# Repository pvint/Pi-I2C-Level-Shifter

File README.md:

# Pi-I2C-Level-Shifter
Level shifter to connect I2C bus on the Pi to +5v or other voltage devices (hardware)

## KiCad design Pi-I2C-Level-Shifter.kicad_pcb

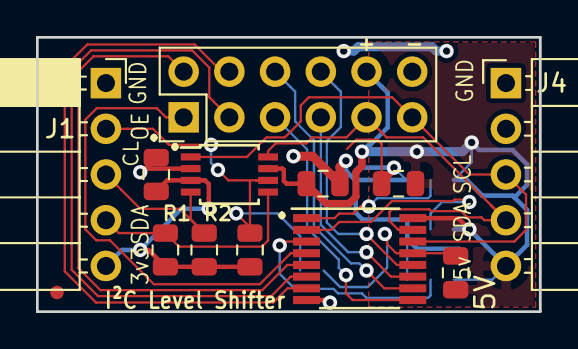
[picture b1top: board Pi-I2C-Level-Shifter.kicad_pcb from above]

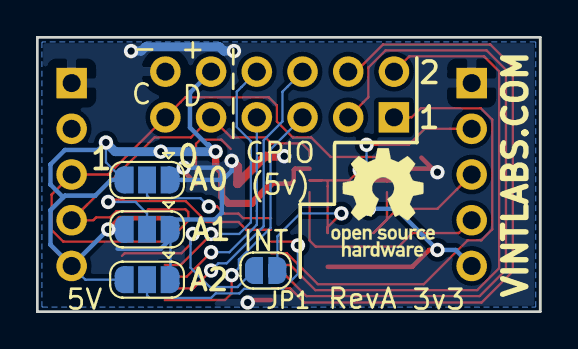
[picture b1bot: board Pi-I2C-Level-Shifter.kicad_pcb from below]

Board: 2 copper layers, 27.9 x 15.2 mm, 16 parts (4 on the bottom side), 20 nets.

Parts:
C1, C2, C3: 0.1uF; C_0805_2012Metric
J1: Conn_01x05; PinSocket_1x05_P2.54mm_Horizontal
J2: Conn_02x06_Odd_Even; PinHeader_2x06_P2.54mm_Vertical
J4: Conn_01x05; PinHeader_1x05_P2.54mm_Horizontal
JP1: SolderJumper_2_Open; SolderJumper-2_P1.3mm_Open_RoundedPad1.0x1.5mm
JP2, JP3, JP4: SolderJumper_3_Open; SolderJumper-3_P1.3mm_Open_RoundedPad1.0x1.5mm
R1, R2, R3, R4: 10k; R_0805_2012Metric
U1: TXB0102DCT; TSSOP-8_3x3mm_P0.65mm
U2: TCA9534; TSSOP-16_4.4x5mm_P0.65mm

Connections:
A0: JP4.2, U2.1
A1: JP3.2, U2.2
A2: JP2.2, U2.3
Earth: C1.2, C2.2, C3.2, J1.1, J2.12, J4.1, JP2.1, JP3.1, JP4.1, U1.2, U2.8
unnamed: JP1.2, R4.2, U2.13
OE: J1.2, JP1.1, R3.2, U1.6
P0: J2.1, U2.4
P1: J2.2, U2.5
P2: J2.3, U2.6
P3: J2.4, U2.7
P4: J2.5, U2.9
P5: J2.6, U2.10
P6: J2.7, U2.11
P7: J2.8, U2.12
SCLa: J1.3, R2.2, U1.4
SCLb: J2.11, J4.3, U1.1, U2.14
SDAa: J1.4, R1.2, U1.5
SDAb: J2.9, J4.4, U1.8, U2.15
Vcca: C1.1, J1.5, R1.1, R2.1, R3.1, U1.3
Vccb: C2.1, C3.1, J2.10, J4.5, JP2.3, JP3.3, JP4.3, R4.1, U1.7, U2.16

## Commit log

2018-11-11 Initial Import
2018-11-11 Added 5v GPIO (8 bits)
2018-11-11 Added fiducial
2018-11-11 Created gerbers
2018-11-11 Remove Ref on fiducial
2018-11-11 Silk edits
